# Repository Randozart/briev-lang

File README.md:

# Briev: A Programming Language
<sub>(Briev is pronounced and was formerly known as 'Brief', but that name was overrepresented.)</sub> 
### TL;DR

Briev is a programming language with the following features:

- Contract driven partial correctness verification (without needing to write essays of formal proof)
- Partially declarative, partially imperative, functional invariant based programming
- Invariant based runtime optimization (with execution speed at parity, or even better than C in several cases)
- Backend independence through state-management based syntax and backend handling of intrinsics
- Backend targeting by extension (`.bv`, `.ebv`, `.rbv`, `.abv`, `.sbv`), plus the auxiliary assembly dialect (`.bad`) and the `.beast` AST format
- A lightweight systems language that handles complexity at compile time
- Core syntax that is equally applicable to the other backends, not just systems programming (auxiliary dialects deliberately drop to lower tiers)
- Inferred command flow through reactive top level `node` declarations
- Memory management by proof through AST graphing
- Syntax which encourages and optimizes for flat programming
- Exhaustive `match` with enum construction — patterns are checked, missing arms are errors
- First-class function values — pass any named function where a callable type is expected
- Typed event ports on objects (SPEC §9.5) with deterministic event delivery
- Legible metaprogramming syntax for macros and compiler plugins with intermediate `.beast` AST files for understanding how the compiler transforms the code
- The Metropolitan FFI which adapts compiled Briev code to any and every other programming language by adapting their calling and memory conventions through the Metropipe and GLUE system
- Helpful compiler hints on failed compilation — did-you-mean suggestions, removed-form diagnostics with fix paths
- Optional Python-like indent-based syntax for those who despise curly braces through the opt-in `.f` dotted profile
- Optional extra strictness through the `.s` dotted profile — representation fallbacks become hard errors
- A conformance sweep that requires every source file in the repo to parse and typecheck — regressions find themselves
- Extensible compile-time literals
- A highlighter shipped with the repo

And for those people for whom this is very important, even if the language itself is already robust enough:

- A cute mascot called _Syn_

| <br/> <p align="center">*Syn*, the Cybersphinx<p> <p align="center"><sup><sub>(For those people who like a mascot to come with their language)</sup></sub><p> | <br/><p align="center">**Briev**<p><br/><p align="center">**Electronics Briev**<p><br/><p align="center">**Accelerated Briev**<p> | <br/><p align="center">**Rendered Briev**<p><br/><p align="center">**Data Briev**<p><p align="center">**Silicon Briev**<p> |
|---|---|---|

## Briev Doesn't Break

Briev is a contract-enforced language designed for building verifiable state machines. It treats program execution as a series of verified state transitions rather than sequential instructions. The file extension selects the compilation target. Each one optimizes the same contract-proven logic for a different material:

| Extension | Variant | Compiles to |
|-----------|---------|-------------|
| `.bv` | **Briev** | LLVM native binary (optional SPIR-V offload) |
| `.rbv` | **Rendered Briev** | WASM + JS shim (browser bundle) |
| `.ebv` | **Electronics Briev** | Electronics backend (component laws, ERC, netlists) |
| `.abv` | **Accelerated Briev** | SPIR-V GPU kernel |
| `.sbv` | **Silicon Briev** | CIRCT hardware description (Verilog/VHDL) |
| `.dbv` / `.dbvl` | **Data Briev** | Configuration data parsed by Briev itself |

The main sources of inspiration are Rust (by Graydon Hoare and the Rust community) and Dialog (by Linus Åkesson). Specifically the fact that both have a very strict compiler, that catches bad code before it ever compiles, simply through smart conventions. Especially the declarative nature is inspired by Dialog, as a direct successor of Prolog, since Dialog showed that setting up a series of predicates could be sufficient to have a compiler figure out a complex runtime capable of simulating a world. And the reactor loop? That was inspired by, well... React. As such, everything in Briev is designed to, in some way, aid in predictable runtime cascades. You set up the first billiard ball, and based on the variables present describing the overall "state", the rest of the balls predictably scatter.

Note that much of this language design was inspired by designing a language that would be impossible for an LLM to get wrong. Therefore it feels important to me to disclaim a lot of AI has been used in building this compiler. The design is fully my own (Randy Smits-Schreuder Goedheijt), but much of the programming was handled by LLMs, and the verification by hand and a series of unit tests (which LLMs somehow manage to cut the corners of). As such, you will find comments, markdown files and many more typical signs of LLM usage in this repository. These all exist to help steer the LLM into *correctly* modifying and applying the design decisions I have made, as it would otherwise be prone to hallucinate a novel language like this. Ergo, you will find a veritable library of markdown files written by AI, just to make sure everything got documented as I went.

If you've gotten this far, I thank you for reading, and I hope you will have enjoyed your *Briev* time here so far.

Regards,

**Randy**

## The Thesis: Topology over Timing

When we sit down to write software, write specifications and build systems, the first thing we do is not make a list of commands. We write a flowchart.

And yet, despite us knowing precisely what needs to hold true at each step, many languages offer us no way to express this knowledge. Not easily at least.

Most programming languages are built around _operations in sequence_. Briev describes the _sequence of operations_ — the spatial connections between logical states.

*   **Logic as a Map:** Briev defines a world where roads exist all at once. The "sequence" is then better called a _connection_, not the _timing_.
*   **Physical Isomorphism:** Because the logic defines a _shape_ rather than a _schedule_, it adapts to the physics of its material:
    *   **In Software:** The compiler hires a worker (the CPU) to walk these roads in order.
    *   **In Hardware:** The compiler builds the roads directly out of copper.
*   **Variable Logic:** The logic remains invariant while the material changes. A square is a square whether it's drawn in the sand or forged in steel.

Where does this thesis end? Honestly: we do not know yet. It started with native code and has so far held — sometimes to our own surprise — on GPU, web, embedded, and toward silicon. The claim is the thesis; the boundary is discovered by benchmarks, not asserted.

## Philosophical Pillars

### All operations are expressed in nodes, and only nodes and transactions can call operations. They either complete fully, or not at all.

Nodes and transactions are inherently cyclical. If you properly define a postcondition a cyclically executed transaction will eventually reach, it automatically starts behaving like a loop, but one that can predictably halt. A transaction with `[pre][post]` converges when the precondition becomes false. This means the postcondition describes the terminal state, and the precondition is the loop condition. You do not write `while (counter < 100)` — the precondition `[counter < 100]` already says "keep running while this holds." The goal-based postcondition `[counter == 100]` expresses the termination state.

Contracts here are predicates: you state how you intend the code to run; the analyses check the program against that intent and consume the contracts as the shape of the graph. And the all-or-nothing shape is preventive — partial-update cascades are a bug class this design keeps from ever forming.

### Briev doesn't need you to be correct, it just needs you to be right.

The contract logic often just requires you to declare either the precondition or postcondition, not both. Contracts are simultaneously specification AND optimization input. In most languages, types/specs are safety rails that constrain what you can do. In Briev, they're also what the optimizer feeds on. The more you declare, the more the compiler can prove, and the faster your program runs. In practice one-sided contracts are usually sufficient; declaring both sides is harder to get right, but pays off when you can state them.

### Execution is inferred, not prescribed.

Programs are declared through a combination of variables, definitions and transactions. The entire program runs on a non-polling reactor loop. It indexes which variable changes lead to which `node` preconditions being fulfilled, and fires them automatically when it's their time to act. Because these paths are laid out predictably, the compiler has great leeway in folding these paths. If X through A, B and C will always lead to Y with side-effect Z, the compiler will simply draw a short route from X to YZ.

The guarantee is Prolog's and Dialog's: *that which must follow, follows, from declaration alone.* For the software that genuinely needs predictability — a declared sequence, a memory layout — `seq` discloses that intent. It exists for correctness and legibility, never as a rescue for failed inference.

### No magic, but honest compromises.

Every function and keyword in Briev must be traceable to a source following the same rules as every other definition. If it looks like `foo(x)`, it is user-defined. Period. The exception is `#`-suffixed intrinsics like `PrintInt#`, `Sqrt#`, `Load#`. These are baked into the AST but explicitly marked with the `#` at every call site. You can never mistake `sqrt` for `Sqrt#`. The `#` is the compiler saying "I have a hand in this one."

The compromises are honest too: escape hatches exist (`.bad`'s acknowledge tier, authority-based bootstrap postconditions), but they are marked, auditable, and never silent. Nothing hidden — not nothing available.

### Contracts are optimization fuel, not a correctness tax.

In most languages, a precondition or assertion is you doing the compiler a favor. In Briev, the contract *is* the optimization input. A precondition like `[x < N]` does more than guard the transaction. The compiler uses this information to emit range metadata on field loads, which lets LLVM eliminate bounds checks. More contracts means more metadata, which means faster code. Safety enables speed.

So instead of thinking *"safety checks slow me down, I will add them later"*, think *"the compiler cannot optimize what it cannot prove."* Write the contract first. The performance follows.

The deeper thesis: undefined behavior is a patch on languages that never let the programmer codify their intent. LLVM assumes; Briev lets you state. The compiler earns the same levers through proof instead of asserting them — a proven transform applies where an assumed one can silently lie.

### Derivation, not recognition.

The compiler never recognizes *which* algorithm you wrote — it derives code from the facts and proofs you declared: bounds, disjointness, associativity, iteration structure, layout intent. A trusted language must turn your algorithm into the best code it is capable of; recognizing particular shapes fails past and future computer scientists by penalizing their algorithms with our ignorance. If an algorithm works well, there is a reason, and a general shape to be discovered — it belongs in declared structure, never in a compiler match arm. Hand-written kernels still exist, but as disclosed, retirement-gated loans: they retire when the general machinery reaches their numbers.

### The compiler's optimum must be expressible in Briev.

C's compiler has been smarter than C for forty years because C cannot state intent. Briev closes that loop: every technique the compiler uses must be buildable in the language itself — in stdlib, metaprogramming, and disclosed hardware primitives — so no trick is forever locked behind a compiler change. The acceptance test has run once, for real: a contributor's university-thesis algorithm, compiled with zero compiler changes, matched hand-optimized C++ — more stable, at roughly equal speed.

### Keywords are for correctness, never speed.

Speed pragmas demand the programmer know the compiler's insides to predict their effect. A good compiler should know, or the language needs better syntax. So nobody writing Briev needs obscure keywords for fast code: the default is the fastest code for the declared semantics, and a keyword-beaten default is a compiler bug. Keywords (`seq`, `vol`, `atomic`, `sync<g>`, ...) express intended *behavior* the efficient default cannot — and anything the compiler handles directly is disclosed with `#`.

### Friction is a signal...

There is no `if/else` in Briev. There are `when` guards: `when condition { body };`. This is not an omission. A guard forces you to ask "what must be true for this to execute?" rather than "which branch do I take?" For branching over values, there is exhaustive `match`. The friction is the point.

Honestly: `when` is cognitive engineering, not a proof mechanism — it keeps code flat, for humans and for the machines that read after them, and the rename decouples the construct from `if`'s baggage. The proof machinery lives in `match`'s exhaustiveness.

### ...but the compiler must help you through it.

Friction without explanation is frustration. Every rejected construct tells you *why* and *what to do instead*. If the compiler says "no," it says "here is the path I can accept." Misspellings get did-you-mean suggestions. Removed forms explain what replaced them. Reserved words say why they're reserved. The friction exists to make you think, not to waste your time.

### Concurrency is explicit.

The compiler refuses to guess whether two reactive nodes may fire together. When it proves two nodes *can* run simultaneously, it demands the author classify the pair — `async` on both (simultaneous firing, acknowledged) or `sync<g>` on both (a group barrier). Concurrency gets a visual artifact of intent on the page, legible to the compiler and to the next reader alike.

## Quick Start

### 1. Build the Compiler

```bash
cargo build --release

# Run the full test suite (2900+ tests)
cargo test --lib && cargo test --bin brievc
```

### 2. Create Your First Program

Create `counter.bv`:

```briev
let count: Int = 0;

node increment [count < 10][count == 10] {
    count = count + 1;
    term;
};
```

The node fires repeatedly while the precondition `[count < 10]` holds. When the goal `[count == 10]` is reached, it stops. The compiler checks the program against your declared intent, proves what it can, and reports what it can't — the honest boundary is visible, not hidden. SPEC §10.7 states exactly which declarations and constructs that boundary currently covers.

### 3. Compile and Run

```bash
# Type-check only (fast)
./target/release/brievc check counter.bv

# Compile to a native binary (LLVM → machine code)
./target/release/brievc build counter.bv

# Emit LLVM IR instead of a binary
./target/release/brievc build counter.bv --llvm

# Format canonically (round-trip safe)
./target/release/brievc fmt counter.bv --stdout

# Or scaffold a new package (folio.toml + an entry node) and run a program
./target/release/brievc init hello
./target/release/brievc run <file.bv>
```

## Language Variants

The file extension selects which backend compiles your program (or, for `.beast`, which serialized form is emitted). Each variant targets a different material:

| Type | File Ext | Description | Compilation Target | Status |
|------|----------|-------------|-------------------|--------|
|  **Briev** | `.bv` | General-purpose systems logic | LLVM → native binary, optional SPIR-V offload | **Stable** |
|  **Accelerated Briev** | `.abv` | GPU compute kernel | SPIR-V (+ PTX tier) | **Functional** |
|  **Rendered Briev** | `.rbv` | Reactive web UI | WASM + JS shim | **Functional** |
|  **Electronics Briev** | `.ebv` | Electronics logic (component laws, ERC) | Electronics backend | **In development** |
|  **Silicon Briev** | `.sbv` | Hardware logic graph | CIRCT → Verilog/VHDL | **Experimental** |
|  **Data Briev** | `.dbv` / `.dbvl` | Configuration data | Parsed by Briev itself | **Stable** |
|  **BAD** | `.bad` | Briev Assembly Dialect — portable assembly, universal core ISA, per-architecture dispatch | Cross-target native (x86_64, aarch64, riscv64, thumbv7m, PTX) | **Functional** |
|  **Beast** | `.beast` / `.beastpack` | AST s-expression serialization for metaprogramming | `--emit-beast` format — not a compiled surface | **Format** |

**Stability legend:** *Stable* = daily use; *Functional* = proven end-to-end (correctness gates green on all lanes / real-browser verified), with performance and surface work continuing; *In development / Experimental* = surface under construction; *Format* = serialized data for tooling, not a compiled surface.

Bare-metal targets (riscv64, Arm Cortex-M) compile from plain `.bv` via target triples — QEMU-verified, no C runtime.

Dotted profiles add strictness: `.s.bv` enables strict mode (representation fallbacks become errors).

## Auxiliary Dialects

Two auxiliary dialects and their packaging formats sit alongside the six main dialects:

- **`.bad` — Briev Assembly Dialect.** Portable assembly: a universal core ISA, `target =>` per-architecture dispatch sites, positional label contracts. Cross-target (x86_64, aarch64, riscv64, thumbv7m, plus the `ptx` family for NVIDIA kernels), with QEMU-verified boot examples. On top of the raw layer sits **assembly+**: symbolic values, `when`/`loop`/`while`, inline and callable `defn`s, `bootstrap`/`data`, and `declarations` (register pins, `extern fn`/`extern data`, `stack N`); engine verbs live in `std/bad/engine.bad`. Compile with `brievc bad file.bad --target <triple>`. Pure `.bad` QEMU boot gates (rv64, aarch64, x86 multiboot): `tests/bare/qemu-rv64-boot-plus-bad.sh`, `tests/bare/qemu-aarch64-boot-plus-bad.sh`, `tests/bare/qemu-multiboot.sh`.
- **`.beast` / `.beastpack` / `.bounty`** — AST s-expression serialization (`--emit-beast`) for legible metaprogramming, typed-AST packaging, and portable distribution. Formats, not compiled surfaces.

## Key Features

### 1. Contracts First

Every transaction declares what must be true **before** and what must be true **after**:

```briev
txn withdraw [balance >= amount][balance >= 0] {
    balance = balance - amount;
    term;
};
```

The compiler verifies reachability of the goal and checks the declared intent — proving what it can and reporting what it can't.

### 2. Reactive by Default

Nodes fire automatically when preconditions are met:

```briev
node auto_save [dirty == true][dirty == false] {
    Save#(buffer);
    dirty = false;
    term;
};
```

No event handlers. No polling. Just logic.

### 3. Exhaustive Match, No if/else

```briev
match value {
    Ok(v) => Print#(v),
    Err(msg) => Print#(0 - 1),
};
```

One-sided execution uses `when` guards. The compiler enforces exhaustiveness — missing cases are errors, unreachable arms are errors.

### 4. Enum Construction

Variants are first-class values:

```briev
enum Result<T, E> {
    Ok(T),
    Err(E)
};

defn divide(a: Int, b: Int) -> Result<Int, String> {
    when b == 0 { term Err("division by zero"); };
    term Ok(a / b);
};
```

Constructors (`Ok(v)`, `Err(e)`) type-check against the enum's declared params. Pattern matching extracts payloads with full exhaustiveness checking.

### 5. Function Values

Named functions flow into callable-typed parameters:

```briev
defn apply(f: (Int, Int) -> Bool, a: Int, b: Int) -> Bool {
    term f(a, b);
};

// Pass any function matching the signature
let eq = apply(cmp_int, 5, 5);
```

### 6. Ports and Events (SPEC §9.5)

Objects communicate through typed event ports:

```briev
obj Enemy(damage: Event<Damage>) -> died: Event<Int> {
    health: Int;
};
```

Input ports bind at construction; output ports fire via `<-`.

### 7. Metropolitan FFI — GLUE

Export Briev functions as native wrappers for any language:

```bash
brievc export bridge.bv python --out ./py-module
brievc export bridge.bv rust --out ./rust-crate
```

Protocol-path BFS finds the cheapest transform between representations. Identity paths compile to zero instructions at LTO time.

## Conformance Sweep

Every source file under `lib/`, `examples/`, `benchmarks/`, and `.smoke/` must parse and typecheck under its classified profile. This runs as part of `cargo test --lib` — any regression finds itself immediately.

```bash
# Run just the sweep
cargo test --lib conformance_sweep

# Full gate (sweep + suite)
./scripts/conformance.sh
```

Backends declare their supported surface through a capability matrix — programs using unsupported features are rejected with what/why/fix diagnostics.

## Testing

```bash
# Full library test suite (includes conformance sweep)
cargo test --lib

# Binary tests
cargo test --bin brievc

# Specific module
cargo test --lib parser::statements
cargo test --lib backend::llvm::tests

# Check a Briev file
./target/debug/brievc check examples/fizzbuzz.bv
```

---

## Examples

### FizzBuzz (Reactive + Match)
```briev
let n: Int = 100;
let current: Int = 1;

node fizzbuzz [current <= n][current == n + 1] {
    let result: String = match current % 15 {
        0 => "FizzBuzz",
        _ => match current % 3 {
            0 => "Fizz",
            _ => match current % 5 {
                0 => "Buzz",
                _ => current as String,
            },
        },
    };
    println!(result);
    current = current + 1;
    term;
};
```

### Error Handling (Result + Match)
```briev
import { is_ok } from "std/result";

defn divide(a: Int, b: Int) -> Result<Int, String> {
    when b == 0 { term Err("division by zero"); };
    term Ok(a / b);
};

defn safe_divide(a: Int, b: Int) -> Int {
    let res = divide(a, b);
    term match res {
        Ok(val) => val,
        Err(msg) => 0 - 1,
    };
};
```

### Object Ports (Event-Driven)
```briev
type Damage { amount: Int; };

obj Enemy(damage: Event<Damage>) -> died: Event<Int> {
    health: Int;
};
```

See [examples/](examples/) for more verified programs.

## Learning Briev

1. **[learn-briev/00-welcome.md](learn-briev/00-welcome.md)** — What is Briev?
2. **[learn-briev/01-basics.md](learn-briev/01-basics.md)** — Variables, types, transactions
3. **[learn-briev/02-contracts.md](learn-briev/02-contracts.md)** — Preconditions & postconditions
4. **[learn-briev/03-reactive.md](learn-briev/03-reactive.md)** — Reactive nodes

**Full documentation:**
- [spec/SPEC.md](spec/SPEC.md) — Complete language specification
- [docs/architecture/agent-reference.md](docs/architecture/agent-reference.md) — Language syntax reference

## Contributing

1. Run `./scripts/conformance.sh` before every push
2. Every new source file must pass the conformance sweep
3. Update architecture docs in the same commit as structural changes

### Contributors

- **Otto Westerlund** ([@odecode](https://github.com/odecode)) — static trait-constrained generics and the `.sbv` synthesizability gate; compiler correctness fixes for liveness, `needs_state`, const globals, pointer provenance, tuple/match lowering, imports and call dispatch; the pure-Briev net stack (ByteSink, TCP client/server, HTTP/1.1, WebSocket, Base64, SHA-1); PostgreSQL v3 wire client; strict JSON parsing and stringify; portable browser stdlib and transport; numeric/CSR primitives; the recommender application and browser/WASM work that exercised them; and the cpp-vs-briev experiment whose thesis algorithm became the first live run of the expressiveness-closure acceptance test. See `docs/contributors/otto-westerlund.md`.

## License

Apache-2.0 WITH LLVM-exception — see [`LICENSE`](LICENSE) and [`NOTICE`](NOTICE). Compiled output of Briev programs is exempt from the notice/attribution obligations.

---

*Last updated: 2026-10-25*

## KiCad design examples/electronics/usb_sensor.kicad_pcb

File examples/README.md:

# Briev Compiler

A transactional, contract-enforced language compiler. Briev treats program execution as verified state transitions with mathematical proofs at compile time.

## Status

**Active development.** The core compiler (lexer, parser, typechecker, interpreter) is complete. Rendered Briev (`.rbv`) UI framework is in progress.

## What is Briev?

Briev is a declarative language where:

- **Transactions are contracts.** Every state change is proven valid before execution.
- **No runtime surprises.** The compiler verifies all state transitions, not the runtime.
- **Lock-free concurrency.** Preconditions act as hardware-level gates — no mutexes needed.
- **Formal verification without boilerplate.** Reactive state machines with pre/post conditions.

```briev
let balance: Int = 100;
let withdrawn: Int = 0;

txn withdraw(amount: Int) [amount > 0 && amount <= balance][balance == @balance - amount] {
  &balance = balance - amount;
  &withdrawn = withdrawn + amount;
  term;
};
```

## Installation

```bash
cargo install --path .
```

## Usage

```bash
# Type check without execution
briev check program.bv

# Build/execute
briev build program.bv

# Initialize a new project
briev init my-project

# Add a dependency
briev register <name> --path <location>
```

## Project Structure

```
src/
├── lexer.rs        # Tokenizer
├── parser.rs       # Recursive descent parser
├── ast.rs          # AST definitions
├── typechecker.rs  # Type inference and verification
├── proof_engine.rs # Contract and reachability proofs
├── interpreter.rs  # Reactive execution engine
├── reactor.rs      # Event-driven reactor loop
├── resolver.rs     # Import resolution
├── manifest.rs     # Dependency management (folio.toml)
├── cache.rs        # Incremental compilation cache
├── watch.rs        # File watching
└── main.rs         # CLI
```

## Documentation

| Spec | Description |
|------|-------------|
| [briev-lang-spec.md](spec/briev-lang-spec.md) | Briev language specification |
| [rendered-briev-spec-v4.md](spec/rendered-briev-spec-v4.md) | Rendered Briev (`.rbv`) UI framework |
| [ARCHITECTURE.md](spec/ARCHITECTURE.md) | Compiler architecture decisions |
| [briev-compiler-build-plan.md](spec/briev-compiler-build-plan.md) | Implementation roadmap |

## VSCode Extension

Syntax highlighting for `.bv` and `.rbv` files is included in `syntax-highlighter/`. Install to VSCodium:

```bash
cp -r syntax-highlighter/ ~/.var/app/com.vscodium.codium/data/vscodium/extensions/briev
```

## Rendered Briev (.rbv)

Rendered Briev (`.rbv`) is a reactive UI framework where Briev logic and HTML coexist in a single file.

The Briev logic owns all state; HTML and CSS are declarative projections of that state. No virtual DOM, no component tree — just bindings.

```html
<script type="briev">
  let count: Int = 0;
  txn increment [true][count == @count + 1] {
    &count = count + 1;
    term;
  };
</script>

<view>
  <p b-text="count">0</p>
  <button b-trigger="increment">+</button>
</view>
```

### Compile

```bash
# Compile .rbv to a directory
briev build --backend webstack component.rbv --out dist/
```

This generates:
- `component.rs` - Rust source
- `component_glue.js` - JS event bridge
- `component.css` - Styles
- `component.html` - HTML wrapper

### Build for Browser

The generated Rust needs to be compiled to WASM:

```bash
# Add wasm32 target
rustup target add wasm32-unknown-unknown

# Install wasm-pack
cargo install wasm-pack

# Create dist/Cargo.toml:
[package]
name = "my-component"
version = "0.1.0"
edition = "2021"

[lib]
crate-type = ["cdylib"]

[dependencies]
wasm-bindgen = "0.2"

# Build
cd dist && wasm-pack build --target web
```

### Serve

```bash
# Simple HTTP server
python3 -m http.server 8080
# or
npx serve .
```

Open `http://localhost:8080/component.html`

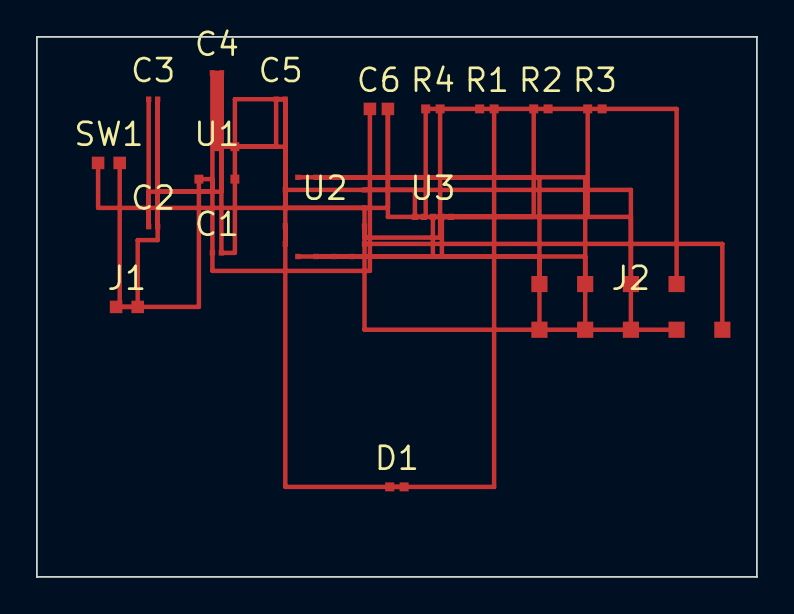
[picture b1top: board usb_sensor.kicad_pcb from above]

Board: 0 copper layers, 40.0 x 30.0 mm, 17 parts (0 on the bottom side), 16 nets.

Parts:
C1, C2, C3, C4, C5: 100n; 0402
C6: 10u; 0805
D1: green; 0603
J1: USB-Micro-B; SMD
J2: SWD; HDR-2x5
R1: 330R; 0603
R2, R3: 4k7; 0603
R4: 10k; 0603
SW1: SPST; SMD
U1: AP2112K-3.3; SOT-25
U2: STM32F042; QFN-32
U3: SHT40; DFN-4

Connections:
N1: C1.2, C2.2, C3.2, C4.2, C5.2, C6.2, J1.2, J2.8, SW1.2, U1.2, U2.2, U3.2, U3.5
N2: D1.1, R1.2
N3: R2.1, U2.12, U3.4
N4: R3.1, U2.11, U3.3
N5: C2.1, C3.1, C4.1, C5.1, J2.9, R1.1, R2.2, R3.2, R4.1, U1.3, U2.1, U3.1
N6: R4.2, SW1.1, U2.6
N7: C1.1, C6.1, J1.1, U1.1
N8: D1.2, U2.3
N9: U1.4, U2.4
N10: J2.3, U2.5
N11: J2.4, U2.7
N12: J2.5, U2.8
N13: J2.6, U2.9
N14: J2.7, U2.10
N15: J2.2, U2.14
N16: J2.1, U2.13
